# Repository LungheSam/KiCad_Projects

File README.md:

# KiCad_Projects
This repository contains KiCad project files for various electronics design projects. It includes schematics, PCB layouts, and related documentation for circuits and systems designed using KiCad.

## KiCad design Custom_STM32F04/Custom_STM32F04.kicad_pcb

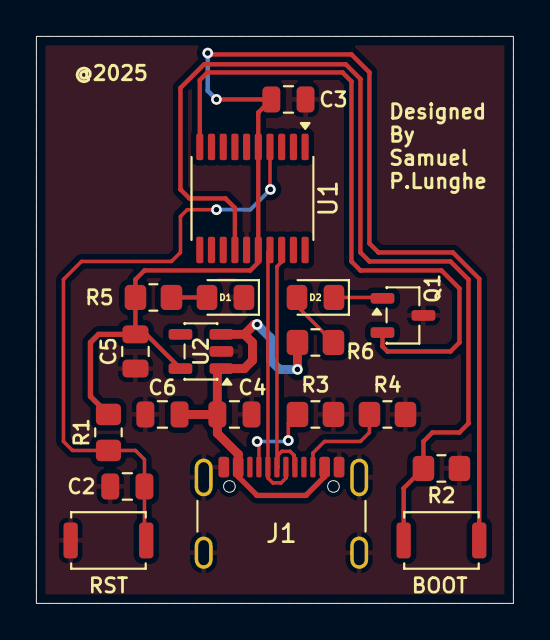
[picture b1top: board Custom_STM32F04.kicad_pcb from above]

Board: 2 copper layers, 26.5 x 31.5 mm, 19 parts (0 on the bottom side), 13 nets.

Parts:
BOOT: SW_Push; SW_Push_SPST_NO_Alps_SKRK
C2: 0.1uF; C_0805_2012Metric
C3, C5, C6: 1uF; C_0805_2012Metric
C4: 10uF; C_0805_2012Metric
D1, D2: LED; LED_0805_2012Metric_Pad1.15x1.40mm_HandSolder
J1: USB_C_Receptacle_USB2.0_16P; USB_C_Receptacle_GCT_USB4105-xx-A_16P_TopMnt_Horizontal
Q1: NMOS; SOT-23-3
R1, R2: 10K; R_0805_2012Metric_Pad1.20x1.40mm_HandSolder
R3, R4: 5.1K; R_0805_2012Metric_Pad1.20x1.40mm_HandSolder
R5, R6: 200; R_0805_2012Metric_Pad1.20x1.40mm_HandSolder
RST: SW_Push; SW_Push_SPST_NO_Alps_SKRK
U1: STM32F042F6Px; TSSOP-20_4.4x6.5mm_P0.65mm
U2: LP5907MFX-3.3; SOT-23-5

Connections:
/3V3: BOOT.2, C3.1, C5.1, R1.1, R5.1, U1.5 (VDDA), U1.16 (VDD), U2.5 (OUT)
/5VUSB: C4.1, C6.1, J1.A4 (VBUS), J1.A9 (VBUS), J1.B4 (VBUS), J1.B9 (VBUS), R6.1, U2.1 (IN), U2.3 (EN)
/BOOT: BOOT.1, R2.1, U1.14 (PB1)
/BUILT_IN_LED: Q1.2 (G), U1.10 (PA4)
/USB_DM: J1.A7 (D-), J1.B7 (D-), U1.17 (PA9/PA11)
/USB_DP: J1.A6 (D+), J1.B6 (D+), U1.18 (PA10/PA12)
/nRESET: C2.1, R1.2, RST.2, U1.4 (NRST)
GND: C2.2, C3.2, C4.2, C5.2, C6.2, D1.1 (K), J1.A1 (GND), J1.A12 (GND), J1.B1 (GND), J1.B12 (GND), J1.S1 (SHIELD), Q1.3 (S), R2.2, R3.2, R4.2, RST.1, U1.15 (VSSA), U2.2 (GND)
unnamed: D1.2 (A), R5.2
unnamed: D2.2 (A), R6.2
unnamed: D2.1 (K), Q1.1 (D)
unnamed: J1.A5 (CC1), R3.1
unnamed: J1.B5 (CC2), R4.1

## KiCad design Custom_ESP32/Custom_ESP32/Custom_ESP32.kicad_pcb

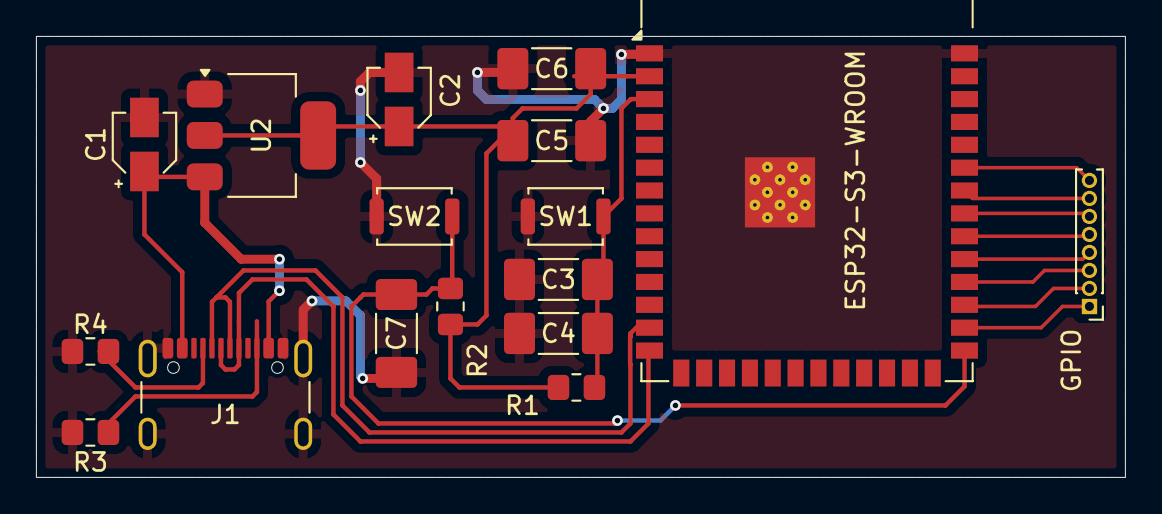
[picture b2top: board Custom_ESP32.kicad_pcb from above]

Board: 2 copper layers, 60.5 x 24.5 mm, 17 parts (0 on the bottom side), 17 nets.

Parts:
C1: 10uF; CP_Elec_3x5.3
C2: 22uF; CP_Elec_3x5.3
C3, C7: 0.1uF; C_1808_4520Metric_Pad1.72x2.30mm_HandSolder
C4, C6: 100nF; C_1808_4520Metric_Pad1.72x2.30mm_HandSolder
C5: 22uF; C_1808_4520Metric_Pad1.72x2.30mm_HandSolder
ESP32-S3-WROOM: ESP32-S3-WROOM-1
GPIO: Conn_01x08_Pin; PinHeader_1x08_P1.00mm_Vertical
J1: USB_C_Receptacle_USB2.0_16P; USB_C_Receptacle_GCT_USB4105-xx-A_16P_TopMnt_Horizontal
R1, R2: 10K; R_0805_2012Metric_Pad1.20x1.40mm_HandSolder
R3, R4: 5.1K; R_0805_2012Metric_Pad1.20x1.40mm_HandSolder
SW1, SW2: SW_Push; SW_Push_SPST_NO_Alps_SKRK
U2: AMS1117-3.3; SOT-223-3_TabPin2

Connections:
+3.3V: C2.1, C5.1, C6.1, ESP32-S3-WROOM.2 (3V3), R1.1, R2.1, U2.2 (VO)
+5V: C1.1, J1.A4 (VBUS), J1.A9 (VBUS), J1.B4 (VBUS), J1.B9 (VBUS), U2.3 (VI)
BOOT: C7.1, ESP32-S3-WROOM.27 (IO0), R2.2, SW2.2
D+: ESP32-S3-WROOM.14 (USB_D+), J1.A6 (D+), J1.B6 (D+)
D-: ESP32-S3-WROOM.13 (USB_D-), J1.A7 (D-), J1.B7 (D-)
ENABLE: C3.1, C4.1, ESP32-S3-WROOM.3 (EN), R1.2, SW1.1
GND: C1.2, C2.2, C3.2, C4.2, C5.2, C6.2, C7.2, ESP32-S3-WROOM.1 (GND), ESP32-S3-WROOM.40 (GND), ESP32-S3-WROOM.41 (GND), J1.A1 (GND), J1.A12 (GND), J1.B1 (GND), J1.B12 (GND), J1.S1 (SHIELD), R3.2, R4.2, SW1.2, SW2.1, U2.1 (GND)
unnamed: ESP32-S3-WROOM.28 (IO35), GPIO.1
unnamed: ESP32-S3-WROOM.29 (IO36), GPIO.2
unnamed: ESP32-S3-WROOM.30 (IO37), GPIO.3
unnamed: ESP32-S3-WROOM.31 (IO38), GPIO.4
unnamed: ESP32-S3-WROOM.32 (IO39), GPIO.5
unnamed: ESP32-S3-WROOM.33 (IO40), GPIO.6
unnamed: ESP32-S3-WROOM.34 (IO41), GPIO.7
unnamed: ESP32-S3-WROOM.35 (IO42), GPIO.8
unnamed: J1.A5 (CC1), R4.1
unnamed: J1.B5 (CC2), R3.1

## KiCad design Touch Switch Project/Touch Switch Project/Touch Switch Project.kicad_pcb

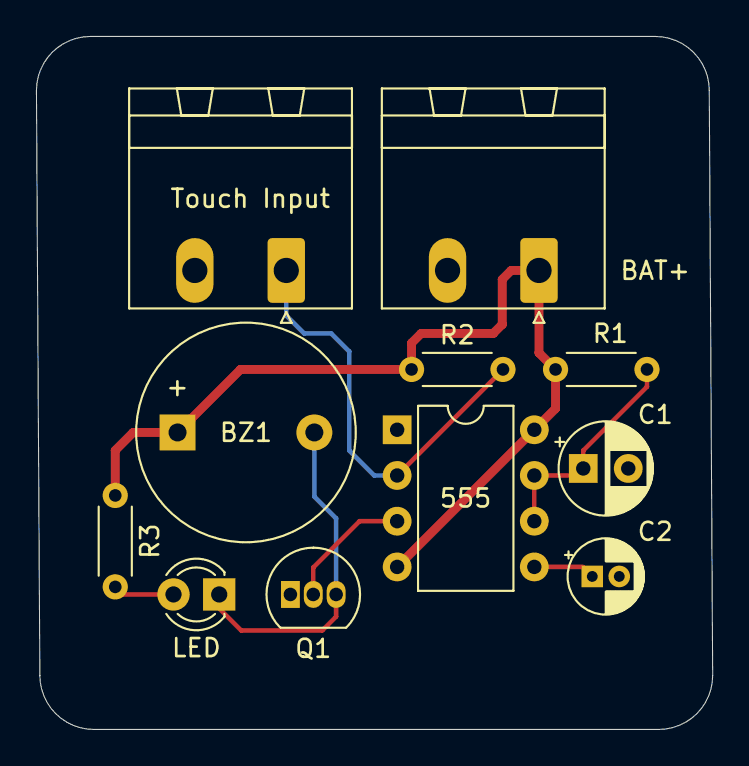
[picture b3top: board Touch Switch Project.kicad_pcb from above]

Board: 2 copper layers, 37.6 x 38.5 mm, 11 parts (0 on the bottom side), 8 nets.

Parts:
555: ICM7555xP; DIP-8_W7.62mm
BAT+: Conn_01x02_Pin; PhoenixContact_MSTBA_2,5_2-G-5,08_1x02_P5.08mm_Horizontal
BZ1: Buzzer; Buzzer_12x9.5RM7.6
C1: 10uF; CP_Radial_D5.0mm_P2.50mm
C2: 10pF; CP_Radial_D4.0mm_P1.50mm
LED: LED; LED_D3.0mm
Q1: 2N3904; TO-92_Inline
R1: 100K; R_Axial_DIN0204_L3.6mm_D1.6mm_P5.08mm_Horizontal
R2: 10M; R_Axial_DIN0204_L3.6mm_D1.6mm_P5.08mm_Horizontal
R3: 220R; R_Axial_DIN0204_L3.6mm_D1.6mm_P5.08mm_Horizontal
Touch Input: Conn_01x02_Pin; PhoenixContact_MSTBA_2,5_2-G-5,08_1x02_P5.08mm_Horizontal

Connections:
GND: 555.1 (GND), BAT+.2, C1.2, C2.2, Q1.1 (E), Touch Input.2
unnamed: BZ1.2 (-), LED.1 (K), Q1.3 (C)
unnamed: LED.2 (A), R3.2
unnamed: 555.2 (TR), R2.2, Touch Input.1
unnamed: 555.3 (Q), Q1.2 (B)
unnamed: 555.5 (CV), C2.1
unnamed: 555.6 (THR), 555.7 (DIS), C1.1, R1.1
VCC: 555.4 (R), 555.8 (VCC), BAT+.1, BZ1.1 (+), R1.2, R2.1, R3.1

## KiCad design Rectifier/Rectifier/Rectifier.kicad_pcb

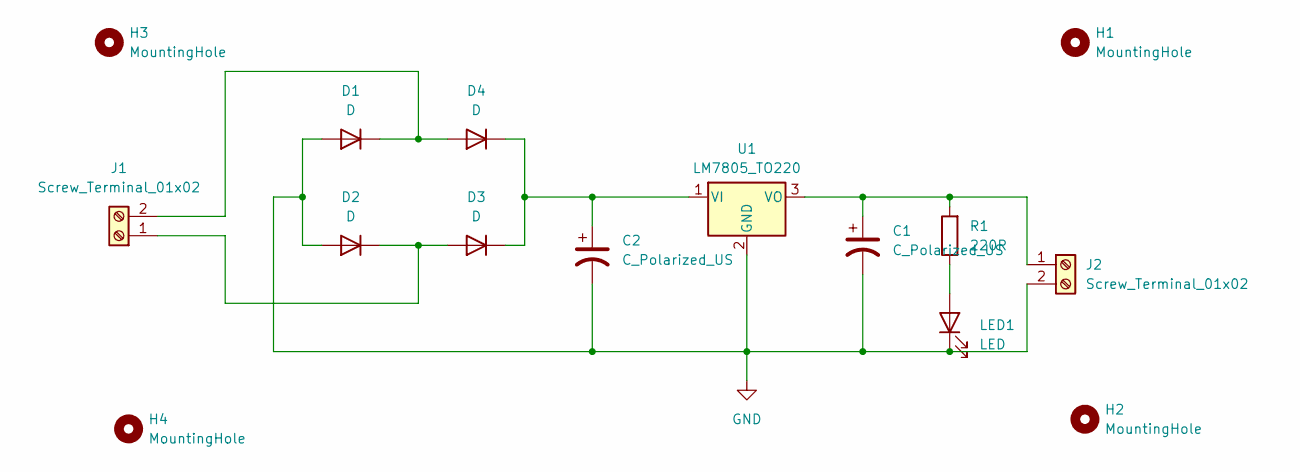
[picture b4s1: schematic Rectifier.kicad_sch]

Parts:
C1, C2: C_Polarized_US; CP_Radial_D5.0mm_P2.00mm
D1, D2, D3, D4: D; D_A-405_P7.62mm_Horizontal
H1, H2, H3, H4: MountingHole; MountingHole_2.5mm
J1, J2: Screw_Terminal_01x02; TerminalBlock_Phoenix_MKDS-1,5-2-5.08_1x02_P5.08mm_Horizont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
LED1: LED; LED_D3.0mm
R1: 220R; R_Axial_DIN0204_L3.6mm_D1.6mm_P5.08mm_Horizontal
U1: LM7805_TO220; TO-220-3_Vertical

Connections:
GND: C1.2, C2.2, D1.2 (A), D2.2 (A), J2.2, LED1.1 (K), U1.2 (GND)
unnamed: D1.1 (K), D4.2 (A), J1.2
unnamed: D2.1 (K), D3.2 (A), J1.1
unnamed: C2.1, D3.1 (K), D4.1 (K), U1.1 (VI)
unnamed: C1.1, J2.1, R1.2, U1.3 (VO)
unnamed: LED1.2 (A), R1.1

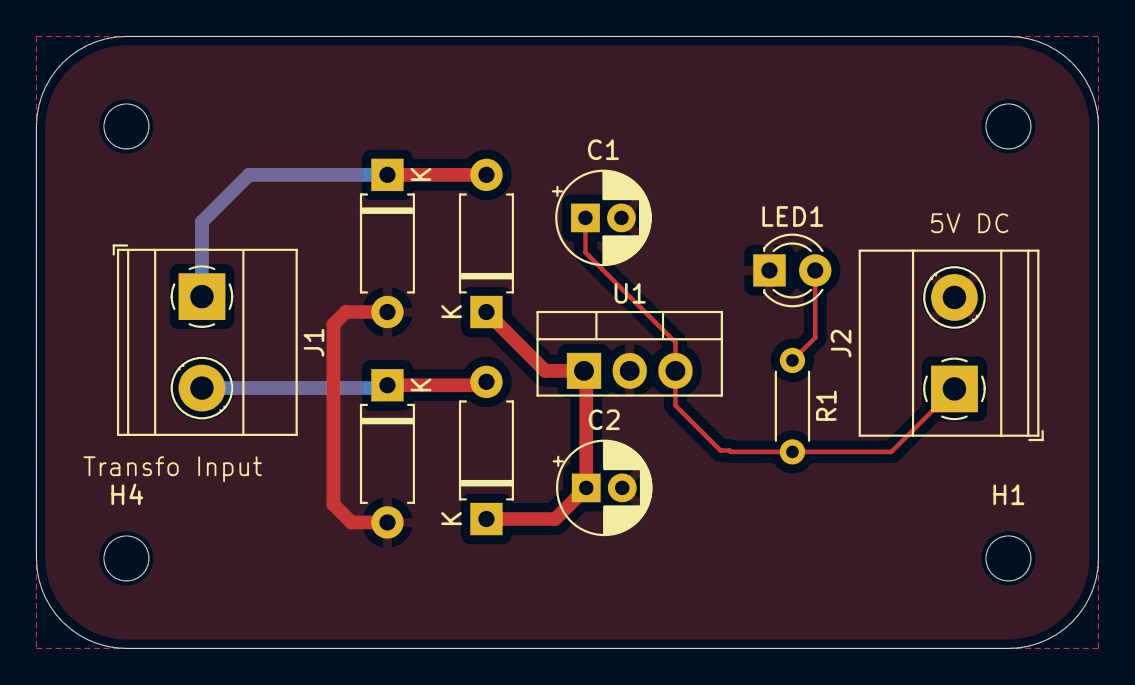
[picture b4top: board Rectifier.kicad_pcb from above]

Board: 2 copper layers, 59.0 x 34.0 mm, 15 parts (0 on the bottom side), 6 nets.

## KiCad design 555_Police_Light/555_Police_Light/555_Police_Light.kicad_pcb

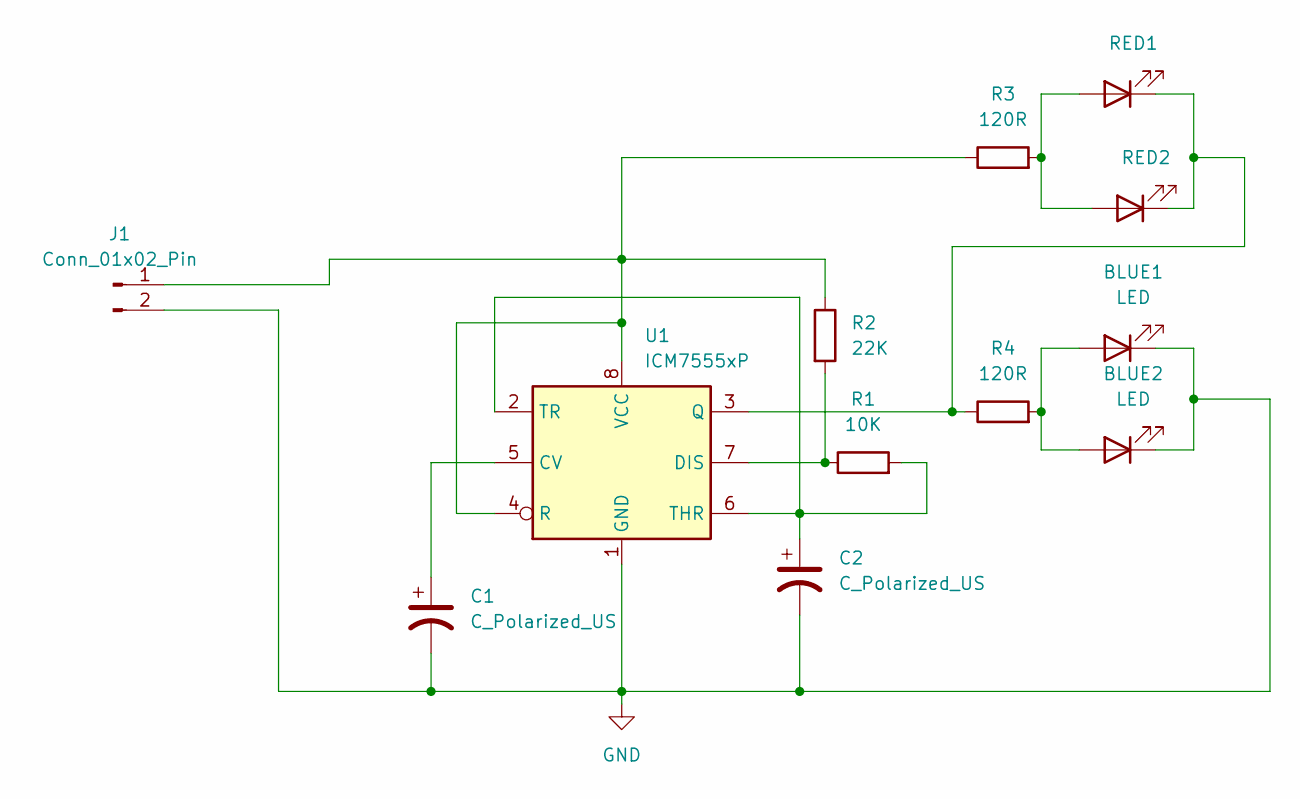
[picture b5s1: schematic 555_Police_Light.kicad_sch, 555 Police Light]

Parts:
BLUE1, BLUE2: LED; LED_D3.0mm_Clear
C1: C_Polarized_US; CP_Radial_D4.0mm_P1.50mm
C2: C_Polarized_US; CP_Radial_D5.0mm_P2.50mm
J1: Conn_01x02_Pin; PinHeader_1x02_P2.00mm_Vertical
R1: 10K; R_Axial_DIN0204_L3.6mm_D1.6mm_P5.08mm_Horizontal
R2: 22K; R_Axial_DIN0204_L3.6mm_D1.6mm_P5.08mm_Horizontal
R3, R4: 120R; R_Axial_DIN0204_L3.6mm_D1.6mm_P5.08mm_Horizontal
RED1, RED2: RED; LED_D3.0mm
U1: ICM7555xP; DIP-8_W7.62mm

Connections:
GND: BLUE1.1 (K), BLUE2.1 (K), C1.2, C2.2, J1.2, U1.1 (GND)
unnamed: BLUE1.2 (A), BLUE2.2 (A), R4.2
unnamed: J1.1, R2.1, R3.1, U1.4 (R), U1.8 (VCC)
unnamed: R3.2, RED1.2 (A), RED2.2 (A)
unnamed: R4.1, RED1.1 (K), RED2.1 (K), U1.3 (Q)
unnamed: C1.1, U1.5 (CV)
unnamed: R1.1, R2.2, U1.7 (DIS)
unnamed: C2.1, R1.2, U1.2 (TR), U1.6 (THR)

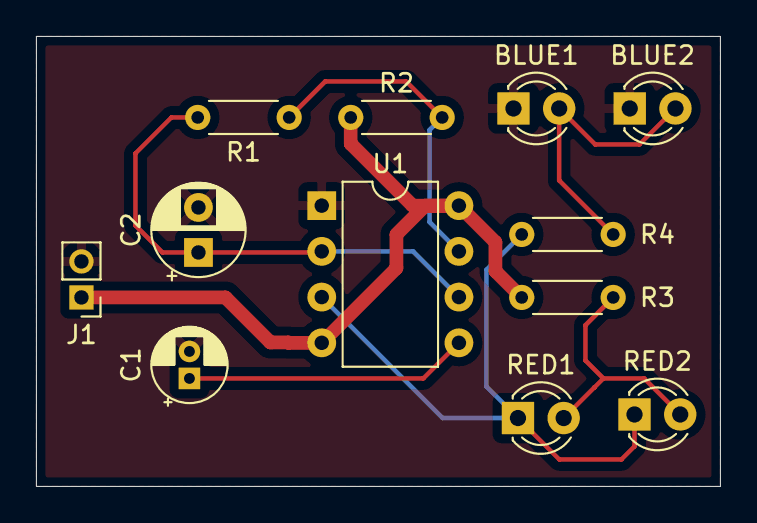
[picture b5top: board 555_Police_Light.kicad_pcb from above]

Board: 2 copper layers, 38.0 x 25.0 mm, 12 parts (0 on the bottom side), 8 nets.

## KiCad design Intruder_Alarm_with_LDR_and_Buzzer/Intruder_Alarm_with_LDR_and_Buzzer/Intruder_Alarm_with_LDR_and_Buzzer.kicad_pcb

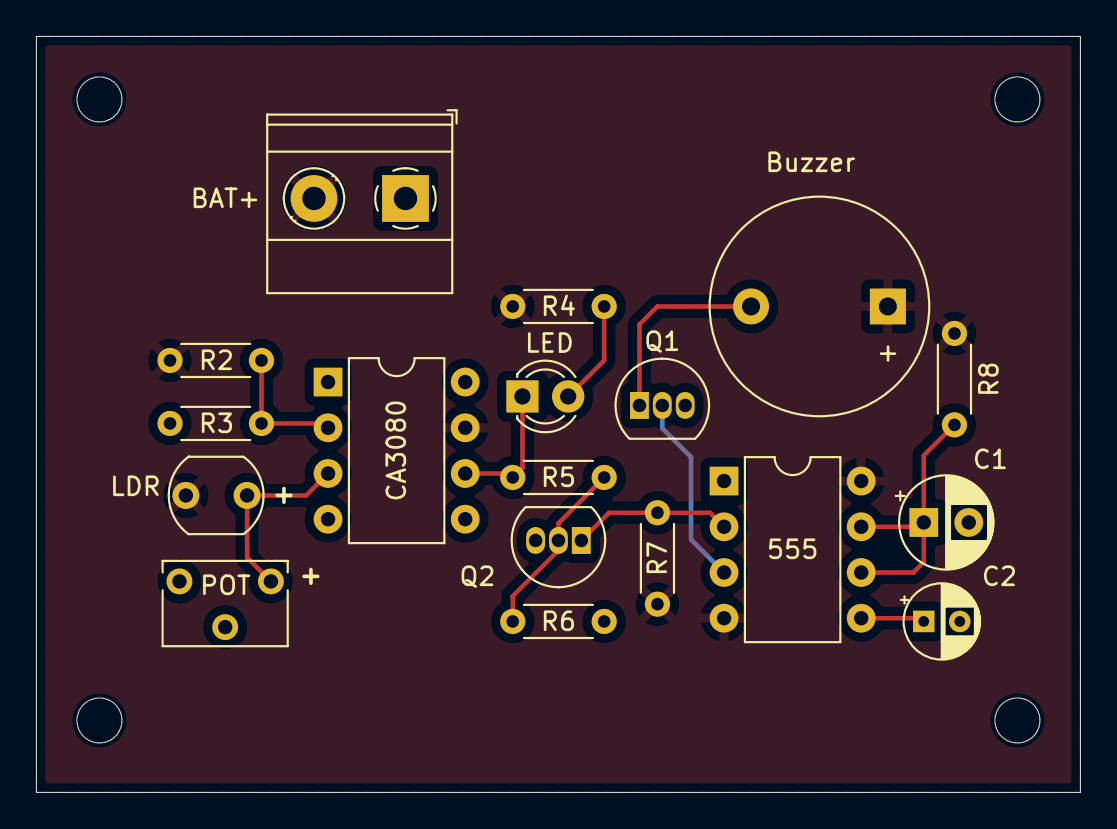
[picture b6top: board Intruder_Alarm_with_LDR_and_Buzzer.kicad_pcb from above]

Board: 2 copper layers, 58.0 x 42.0 mm, 22 parts (0 on the bottom side), 12 nets.

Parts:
555: ICM7555xP; DIP-8_W7.62mm
BAT+: Screw_Terminal_01x02; TerminalBlock_Phoenix_MKDS-1,5-2-5.08_1x02_P5.08mm_Horizont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
Buzzer: Buzzer; Buzzer_12x9.5RM7.6
C1: 10uF; CP_Radial_D5.0mm_P2.50mm
C2: 1nF; CP_Radial_D4.0mm_P2.00mm
CA3080: CA3080; DIP-8_W7.62mm
H1, H2, H3, H4: MountingHole; MountingHole_2.5mm
LDR: LDR07; R_LDR_5.1x4.3mm_P3.4mm_Vertical
LED: LED; LED_D3.0mm
POT: R_Potentiometer; Potentiometer_Bourns_3266W_Vertical
Q1: BC547; TO-92_Inline
Q2: BC557; TO-92_Inline
R2: 47K; R_Axial_DIN0204_L3.6mm_D1.6mm_P5.08mm_Horizontal
R3: 10K; R_Axial_DIN0204_L3.6mm_D1.6mm_P5.08mm_Horizontal
R4: 220R; R_Axial_DIN0204_L3.6mm_D1.6mm_P5.08mm_Horizontal
R5, R7: 1K; R_Axial_DIN0204_L3.6mm_D1.6mm_P5.08mm_Horizontal
R6: 500R; R_Axial_DIN0204_L3.6mm_D1.6mm_P5.08mm_Horizontal
R8: 1M; R_Axial_DIN0204_L3.6mm_D1.6mm_P5.08mm_Horizontal

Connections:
GND: 555.1 (GND), BAT+.1, C1.2, C2.2, CA3080.4 (V-), POT.2, POT.3, Q1.3 (E), Q2.3 (E), R3.2, R6.2
unnamed: Buzzer.2 (-), Q1.1 (C)
unnamed: LED.2 (A), R4.2
unnamed: CA3080.6, LED.1 (K), R5.1
unnamed: 555.3 (Q), Q1.2 (B)
unnamed: Q2.2 (B), R5.2, R6.1
unnamed: 555.2 (TR), Q2.1 (C), R7.2
unnamed: CA3080.3 (+), LDR.2, POT.1
unnamed: CA3080.2 (-), R2.2, R3.1
unnamed: 555.5 (CV), C2.1
unnamed: 555.6 (THR), 555.7 (DIS), C1.1, R8.2
VCC: 555.4 (R), 555.8 (VCC), BAT+.2, Buzzer.1 (+), CA3080.7 (V+), LDR.1, R2.1, R4.1, R7.1, R8.1

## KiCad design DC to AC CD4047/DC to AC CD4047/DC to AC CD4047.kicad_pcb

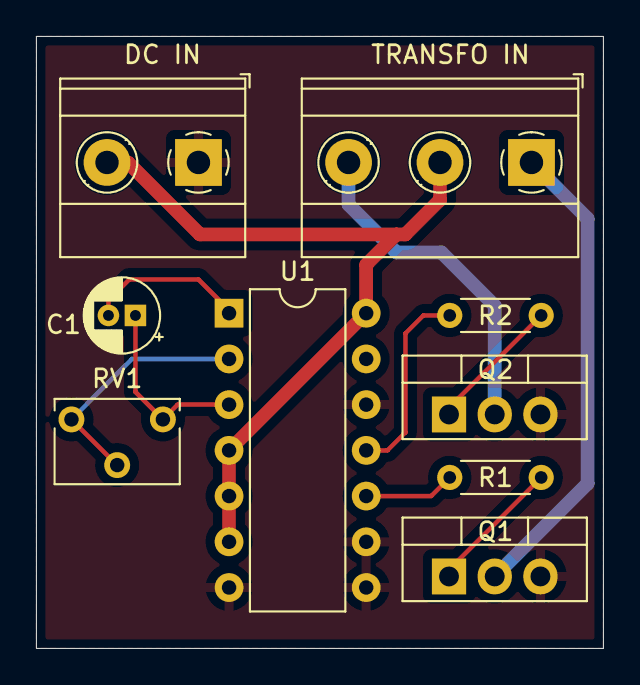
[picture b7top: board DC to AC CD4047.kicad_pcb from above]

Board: 2 copper layers, 31.5 x 34.0 mm, 9 parts (0 on the bottom side), 11 nets.

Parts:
C1: 0.1uF; CP_Radial_D4.0mm_P1.50mm
DC IN: Screw_Terminal_01x02; TerminalBlock_Phoenix_MKDS-1,5-2-5.08_1x02_P5.08mm_Horizont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
Q1, Q2: IRLZ44N; TO-220-3_Vertical
R1, R2: 100; R_Axial_DIN0204_L3.6mm_D1.6mm_P5.08mm_Horizontal
RV1: 22k; Potentiometer_Bourns_3266W_Vertical
TRANSFO IN: Screw_Terminal_01x03; TerminalBlock_Phoenix_MKDS-1,5-3-5.08_1x03_P5.08mm_Horizont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
U1: 4047; DIP-14_W7.62mm

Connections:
GND: DC IN.1, Q1.3 (S), Q2.3 (S), U1.7 (VSS), U1.8 (+TRIGGER), U1.9 (EXT_RESET), U1.12 (RETRIGGER)
unnamed: Q1.2 (D), TRANSFO IN.1
unnamed: Q2.2 (D), TRANSFO IN.3
unnamed: Q1.1 (G), R1.2
unnamed: Q2.1 (G), R2.2
unnamed: C1.2, U1.1 (C)
unnamed: R1.1, U1.10 (Q)
unnamed: RV1.2, RV1.3, U1.2 (R)
unnamed: C1.1, RV1.1, U1.3 (RC_COMMON)
unnamed: R2.1, U1.11 (~Q)
VCC: DC IN.2, TRANSFO IN.2, U1.4 (~ASTABLE), U1.5 (ASTABLE), U1.6 (-TRIGGER), U1.14 (VDD)

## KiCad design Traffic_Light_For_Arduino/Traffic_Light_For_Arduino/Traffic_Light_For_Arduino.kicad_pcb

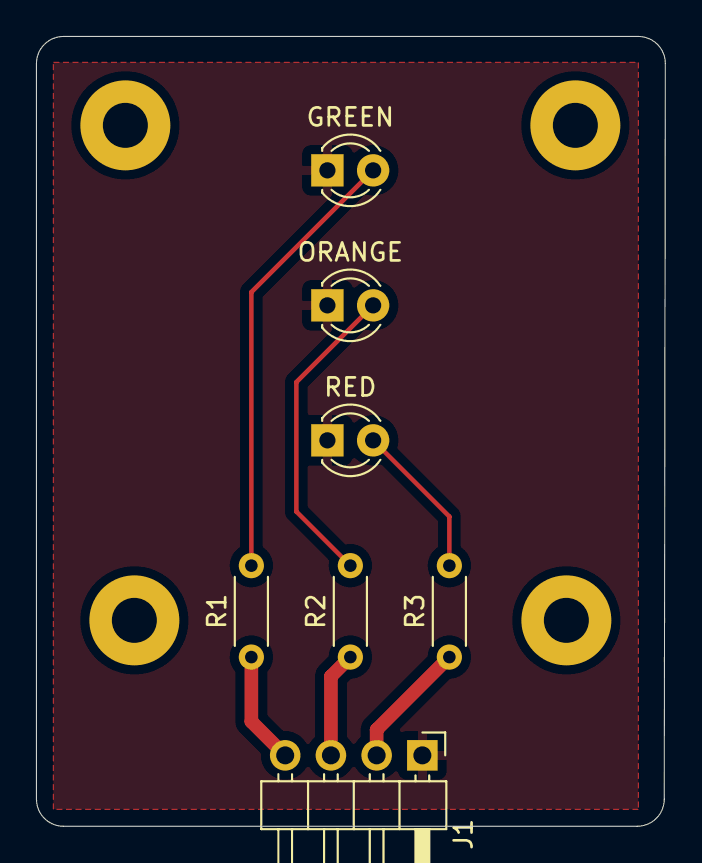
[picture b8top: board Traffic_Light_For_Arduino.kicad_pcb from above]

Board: 2 copper layers, 34.9 x 43.9 mm, 11 parts (0 on the bottom side), 7 nets.

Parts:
GREEN: GREEN; LED_D3.0mm
H1, H2, H3, H4: MountingHole; MountingHole_2.5mm_Pad
J1: Conn_01x04; PinHeader_1x04_P2.54mm_Horizontal
ORANGE: YELLOW; LED_D3.0mm
R1, R2, R3: 220R; R_Axial_DIN0204_L3.6mm_D1.6mm_P5.08mm_Horizontal
RED: RED; LED_D3.0mm

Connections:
GND: GREEN.1 (K), J1.1, ORANGE.1 (K), RED.1 (K)
unnamed: GREEN.2 (A), R1.2
unnamed: ORANGE.2 (A), R2.2
unnamed: R3.2, RED.2 (A)
unnamed: J1.2, R3.1
unnamed: J1.3, R2.1
unnamed: J1.4, R1.1

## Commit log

2025-02-08 Project Touch Switch Added
2025-12-04 Added ESP32 Custom Project
2025-12-07 Added Custom STM32F04 Design
2026-01-10 STM32F04 Project finished

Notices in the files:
Traffic_Light_For_Arduino/Traffic_Light_For_Arduino/Traffic_Light_For_Arduino.kicad_pcb:
License CC BY 4.0
